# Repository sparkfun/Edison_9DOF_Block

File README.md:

SparkFun Edison 9 Degrees of Freedom
=====================

[*SparkFun Edison 9 Degrees of Freedom (DEV-13033)*](https://www.sparkfun.com/products/13033)

The 9DOF board for the Edison uses the STMicro LSM9DS0 9 Degrees of Freedom IMU for full-range motion sensing. This chip combines a 3-axis accelerometer, a 3-axis gyroscope, and a 3-axis magnetometer. By default, the IMU is connected to the Edison through the I2C bus but can be configured to use the SPI bus.

Repository Contents
-------------------
 
* **/Hardware** - Eagle design files (.brd, .sch)
* **/Production** - Production panel files (.brd)

Documentation
--------------
* **[Hookup Guide](https://learn.sparkfun.com/tutorials/sparkfun-blocks-for-intel-edison---9-degrees-of-freedom-block-)** - Basic hookup guide for the Edison 9DOF.
* **[SparkFun Fritzing repo](https://github.com/sparkfun/Fritzing_Parts)** - Fritzing diagrams for SparkFun products.
* **[SparkFun 3D Model repo](https://github.com/sparkfun/3D_Models)** - 3D models of SparkFun products. 
* **[SparkFun Graphical Datasheets](https://github.com/sparkfun/Graphical_Datasheets)** -Graphical Datasheets for various SparkFun products.

License Information
-------------------

This product is _**open source**_! 

Please review the LICENSE.md file for license information. 

If you have any questions or concerns on licensing, please contact techsupport@sparkfun.com.

Distributed as-is; no warranty is given.

- Your friends at SparkFun.

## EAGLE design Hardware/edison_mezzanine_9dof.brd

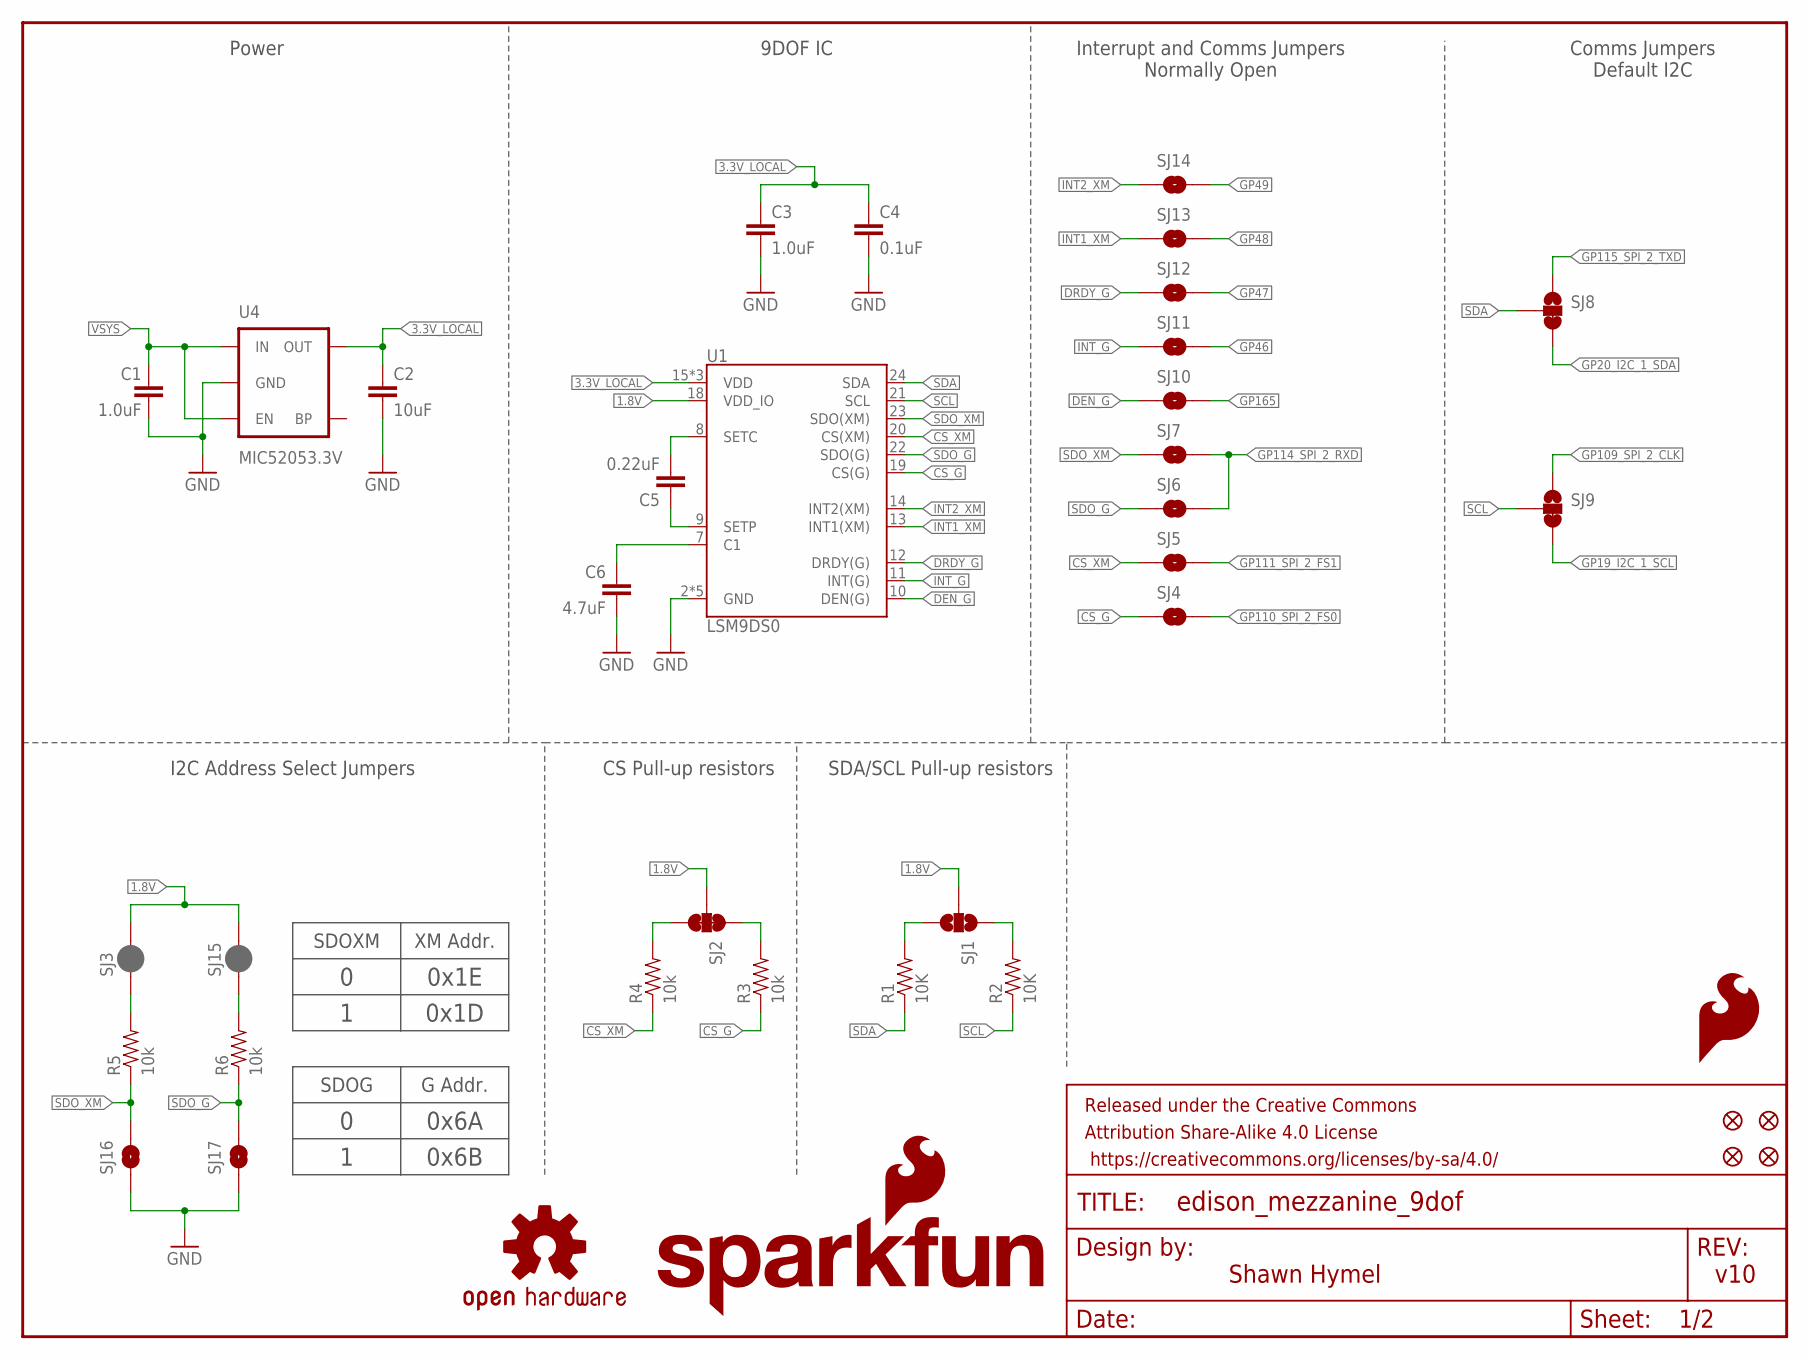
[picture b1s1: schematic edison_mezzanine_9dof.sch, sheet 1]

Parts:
C1, C3: 1.0uF; 0603-CAP
C2: 10uF; 0805
C4: 0.1uF; 0603-CAP
C5: 0.22uF; 0603-CAP
C6: 4.7uF; 0603-CAP
FID1, FID2, FID3, FID4: FIDUCIAL1X2; FIDUCIAL-1X2
FRAME1: FRAME-LETTER; CREATIVE_COMMONS
LOGO1: SFE_LOGO_FLAME.2_INCH; SFE_LOGO_FLAME_.2
LOGO2: OSHW-LOGOS; OSHW-LOGO-S
LOGO3: SFE_LOGO_NAME_FLAME.1_INCH; SFE_LOGO_NAME_FLAME_.1
R1, R2: 10K; 0603-RES
R3, R4, R5, R6: 10k; 0603-RES
SJ1: JUMPER-PAD-3-NOYES_SILK; PAD-JUMPER-3-NO_YES_SILK
SJ2: JUMPER-PAD-3-NC_BY_TRACE; PAD-JUMPER-3-3OF3_NC_BY_TRACE_YES_SILK_FULL_BOX
SJ3, SJ15: JUMPER-PAD-2-NC_BY_PASTE; PAD-JUMPER-2-NC_BY_PASTE_YES_SILK
SJ4, SJ5, SJ6, SJ7, SJ10, SJ11, SJ12, SJ13, SJ14, SJ16, SJ17: JUMPER-PAD-2-NOYES_SILK; PAD-JUMPER-2-NO_YES_SILK
SJ8, SJ9: JUMPER-PAD-3-2OF3_NC_BY_TRACE_SMALL; PAD-JUMPER-3-2OF3_NC_BY_TRACE_YES_SILK_FULL_BOX
U1: LSM9DS0; LGA-24
U4: MIC52053.3V; SOT23-5

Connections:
1.8V: SJ1.2, SJ2.2, SJ3.2, SJ15.2, U1.18 (VDD_IO); also elsewhere on the board
3.3V_LOCAL: C2.1, C3.1, C4.1, U1.15 (VDD), U1.16 (VDD), U1.17 (VDD), U4.5 (OUT)
CS_G: R3.1, SJ4.1, U1.19 (CS(G))
CS_XM: R4.1, SJ5.1, U1.20 (CS(XM))
DEN_G: SJ10.1, U1.10 (DEN(G))
DRDY_G: SJ12.1, U1.12 (DRDY(G))
GND: C1.2, C2.2, C3.2, C4.2, C6.2, SJ16.1, SJ17.1, U1.2 (GND), U1.3 (GND), U1.4 (GND), U1.5 (GND), U1.6 (GND), U4.2 (GND); also elsewhere on the board
GP19_I2C_1_SCL: SJ9.3; also elsewhere on the board
GP20_I2C_1_SDA: SJ8.3; also elsewhere on the board
GP46: SJ11.2; also elsewhere on the board
GP47: SJ12.2; also elsewhere on the board
GP48: SJ13.2; also elsewhere on the board
GP49: SJ14.2; also elsewhere on the board
GP109_SPI_2_CLK: SJ9.1; also elsewhere on the board
GP110_SPI_2_FS0: SJ4.2; also elsewhere on the board
GP111_SPI_2_FS1: SJ5.2; also elsewhere on the board
GP114_SPI_2_RXD: SJ6.2, SJ7.2; also elsewhere on the board
GP115_SPI_2_TXD: SJ8.1; also elsewhere on the board
GP165: SJ10.2; also elsewhere on the board
INT1_XM: SJ13.1, U1.13 (INT1(XM))
INT2_XM: SJ14.1, U1.14 (INT2(XM))
INT_G: SJ11.1, U1.11 (INT(G))
unnamed: C5.1, U1.9 (SETP)
unnamed: C5.2, U1.8 (SETC)
unnamed: C6.1, U1.7 (C1)
unnamed: R3.2, SJ2.1
unnamed: R4.2, SJ2.3
unnamed: R1.2, SJ1.3
unnamed: R2.2, SJ1.1
unnamed: R5.2, SJ3.1
unnamed: R6.2, SJ15.1
SCL: R2.1, SJ9.2, U1.21 (SCL)
SDA: R1.1, SJ8.2, U1.24 (SDA)
SDO_G: R6.1, SJ6.1, SJ17.2, U1.22 (SDO(G))
SDO_XM: R5.1, SJ7.1, SJ16.2, U1.23 (SDO(XM))
VSYS: C1.1, U4.1 (IN), U4.3 (EN); also elsewhere on the board

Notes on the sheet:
I2C Address Select Jumpers
SDA/SCL Pull-up resistors
9DOF IC
Interrupt and Comms Jumpers Normally Open
Comms Jumpers Default I2C
Power
CS Pull-up resistors
SDOXM
XM Addr.
0x1E
0x1D
SDOG
G Addr.
0x6A
0x6B
v10
Shawn Hymel

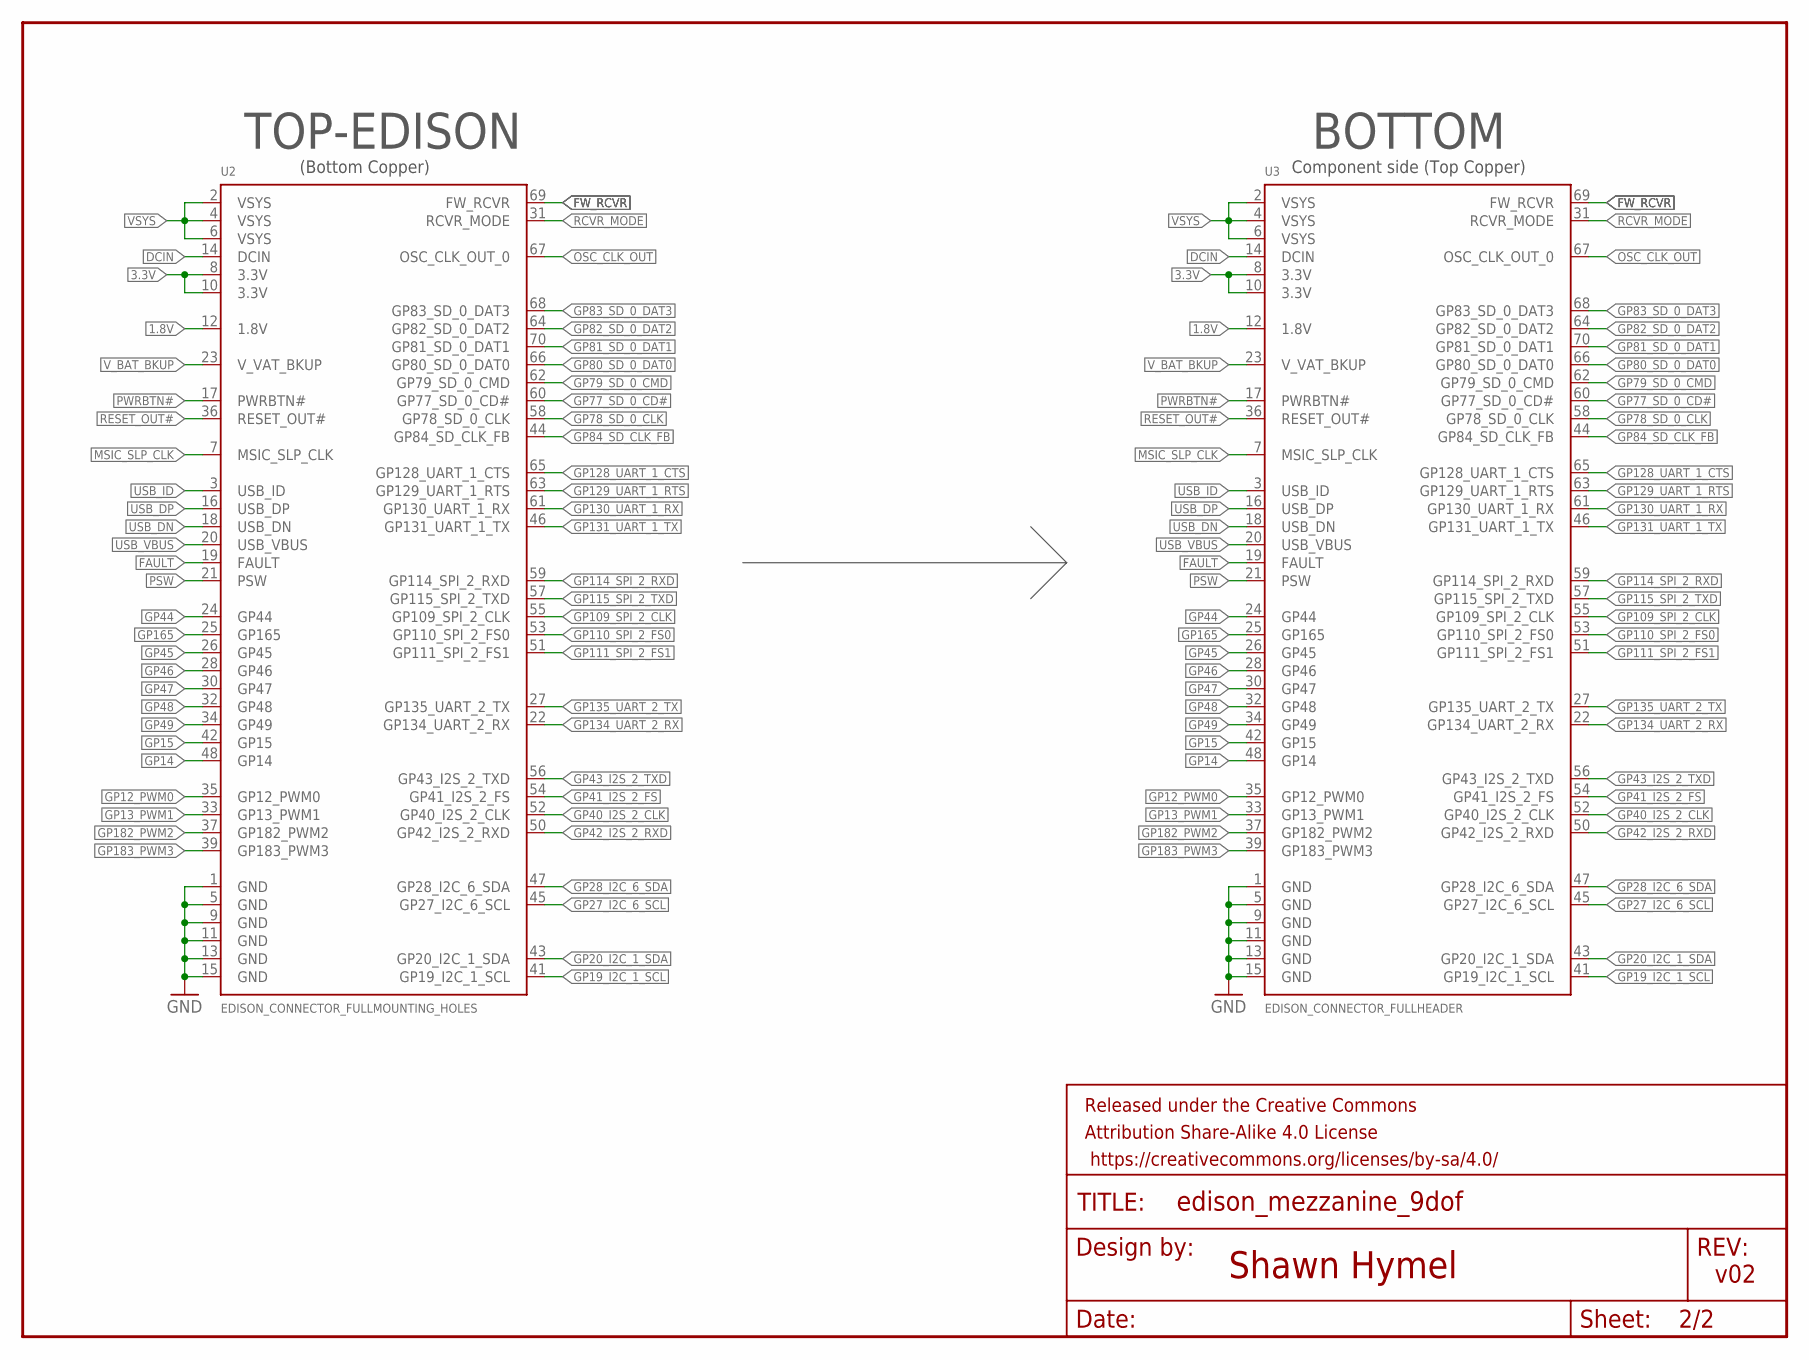
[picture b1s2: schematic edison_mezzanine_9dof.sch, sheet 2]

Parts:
FRAME2: FRAME-LETTER; CREATIVE_COMMONS
U2: EDISON_CONNECTOR_FULLMOUNTING_HOLES; EDISON_DAUGHTER
U3: EDISON_CONNECTOR_FULLHEADER; DF40C-70DP-0.4(51)

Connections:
1.8V: U2.12 (1.8V), U3.12 (1.8V); also elsewhere on the board
3.3V: U2.8 (3.3V), U2.10 (3.3V), U3.8 (3.3V), U3.10 (3.3V)
DCIN: U2.14 (DCIN), U3.14 (DCIN)
FAULT: U2.19 (FAULT), U3.19 (FAULT)
FW_RCVR: U2.69 (FW_RCVR), U3.69 (FW_RCVR)
GND: U2.1 (GND), U2.5 (GND), U2.9 (GND), U2.11 (GND), U2.13 (GND), U2.15 (GND), U3.1 (GND), U3.5 (GND), U3.9 (GND), U3.11 (GND), U3.13 (GND), U3.15 (GND); also elsewhere on the board
GP12_PWM0: U2.35 (GP12_PWM0), U3.35 (GP12_PWM0)
GP13_PWM1: U2.33 (GP13_PWM1), U3.33 (GP13_PWM1)
GP14: U2.48 (GP14), U3.48 (GP14)
GP15: U2.42 (GP15), U3.42 (GP15)
GP19_I2C_1_SCL: U2.41 (GP19_I2C_1_SCL), U3.41 (GP19_I2C_1_SCL); also elsewhere on the board
GP20_I2C_1_SDA: U2.43 (GP20_I2C_1_SDA), U3.43 (GP20_I2C_1_SDA); also elsewhere on the board
GP27_I2C_6_SCL: U2.45 (GP27_I2C_6_SCL), U3.45 (GP27_I2C_6_SCL)
GP28_I2C_6_SDA: U2.47 (GP28_I2C_6_SDA), U3.47 (GP28_I2C_6_SDA)
GP40_I2S_2_CLK: U2.52 (GP40_I2S_2_CLK), U3.52 (GP40_I2S_2_CLK)
GP41_I2S_2_FS: U2.54 (GP41_I2S_2_FS), U3.54 (GP41_I2S_2_FS)
GP42_I2S_2_RXD: U2.50 (GP42_I2S_2_RXD), U3.50 (GP42_I2S_2_RXD)
GP43_I2S_2_TXD: U2.56 (GP43_I2S_2_TXD), U3.56 (GP43_I2S_2_TXD)
GP44: U2.24 (GP44), U3.24 (GP44)
GP45: U2.26 (GP45), U3.26 (GP45)
GP46: U2.28 (GP46), U3.28 (GP46); also elsewhere on the board
GP47: U2.30 (GP47), U3.30 (GP47); also elsewhere on the board
GP48: U2.32 (GP48), U3.32 (GP48); also elsewhere on the board
GP49: U2.34 (GP49), U3.34 (GP49); also elsewhere on the board
GP77_SD_0_CD#: U2.60 (GP77_SD_0_CD#), U3.60 (GP77_SD_0_CD#)
GP78_SD_0_CLK: U2.58 (GP78_SD_0_CLK), U3.58 (GP78_SD_0_CLK)
GP79_SD_0_CMD: U2.62 (GP79_SD_0_CMD), U3.62 (GP79_SD_0_CMD)
GP80_SD_0_DAT0: U2.66 (GP80_SD_0_DAT0), U3.66 (GP80_SD_0_DAT0)
GP81_SD_0_DAT1: U2.70 (GP81_SD_0_DAT1), U3.70 (GP81_SD_0_DAT1)
GP82_SD_0_DAT2: U2.64 (GP82_SD_0_DAT2), U3.64 (GP82_SD_0_DAT2)
GP83_SD_0_DAT3: U2.68 (GP83_SD_0_DAT3), U3.68 (GP83_SD_0_DAT3)
GP84_SD_CLK_FB: U2.44 (GP84_SD_CLK_FB), U3.44 (GP84_SD_CLK_FB)
GP109_SPI_2_CLK: U2.55 (GP109_SPI_2_CLK), U3.55 (GP109_SPI_2_CLK); also elsewhere on the board
GP110_SPI_2_FS0: U2.53 (GP110_SPI_2_FS0), U3.53 (GP110_SPI_2_FS0); also elsewhere on the board
GP111_SPI_2_FS1: U2.51 (GP111_SPI_2_FS1), U3.51 (GP111_SPI_2_FS1); also elsewhere on the board
GP114_SPI_2_RXD: U2.59 (GP114_SPI_2_RXD), U3.59 (GP114_SPI_2_RXD); also elsewhere on the board
GP115_SPI_2_TXD: U2.57 (GP115_SPI_2_TXD), U3.57 (GP115_SPI_2_TXD); also elsewhere on the board
GP128_UART_1_CTS: U2.65 (GP128_UART_1_CTS), U3.65 (GP128_UART_1_CTS)
GP129_UART_1_RTS: U2.63 (GP129_UART_1_RTS), U3.63 (GP129_UART_1_RTS)
GP130_UART_1_RX: U2.61 (GP130_UART_1_RX), U3.61 (GP130_UART_1_RX)
GP131_UART_1_TX: U2.46 (GP131_UART_1_TX), U3.46 (GP131_UART_1_TX)
GP134_UART_2_RX: U2.22 (GP134_UART_2_RX), U3.22 (GP134_UART_2_RX)
GP135_UART_2_TX: U2.27 (GP135_UART_2_TX), U3.27 (GP135_UART_2_TX)
GP165: U2.25 (GP165), U3.25 (GP165); also elsewhere on the board
GP182_PWM2: U2.37 (GP182_PWM2), U3.37 (GP182_PWM2)
GP183_PWM3: U2.39 (GP183_PWM3), U3.39 (GP183_PWM3)
MSIC_SLP_CLK: U2.7 (MSIC_SLP_CLK), U3.7 (MSIC_SLP_CLK)
OSC_CLK_OUT: U2.67 (OSC_CLK_OUT_0), U3.67 (OSC_CLK_OUT_0)
PSW: U2.21 (PSW), U3.21 (PSW)
PWRBTN#: U2.17 (PWRBTN#), U3.17 (PWRBTN#)
RCVR_MODE: U2.31 (RCVR_MODE), U3.31 (RCVR_MODE)
RESET_OUT#: U2.36 (RESET_OUT#), U3.36 (RESET_OUT#)
USB_DN: U2.18 (USB_DN), U3.18 (USB_DN)
USB_DP: U2.16 (USB_DP), U3.16 (USB_DP)
USB_ID: U2.3 (USB_ID), U3.3 (USB_ID)
USB_VBUS: U2.20 (USB_VBUS), U3.20 (USB_VBUS)
VSYS: U2.2 (VSYS), U2.4 (VSYS), U2.6 (VSYS), U3.2 (VSYS), U3.4 (VSYS), U3.6 (VSYS); also elsewhere on the board
V_BAT_BKUP: U2.23 (V_VAT_BKUP), U3.23 (V_VAT_BKUP)

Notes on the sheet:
TOP-EDISON
BOTTOM
Component side (Top Copper)
(Bottom Copper)
Shawn Hymel
v02

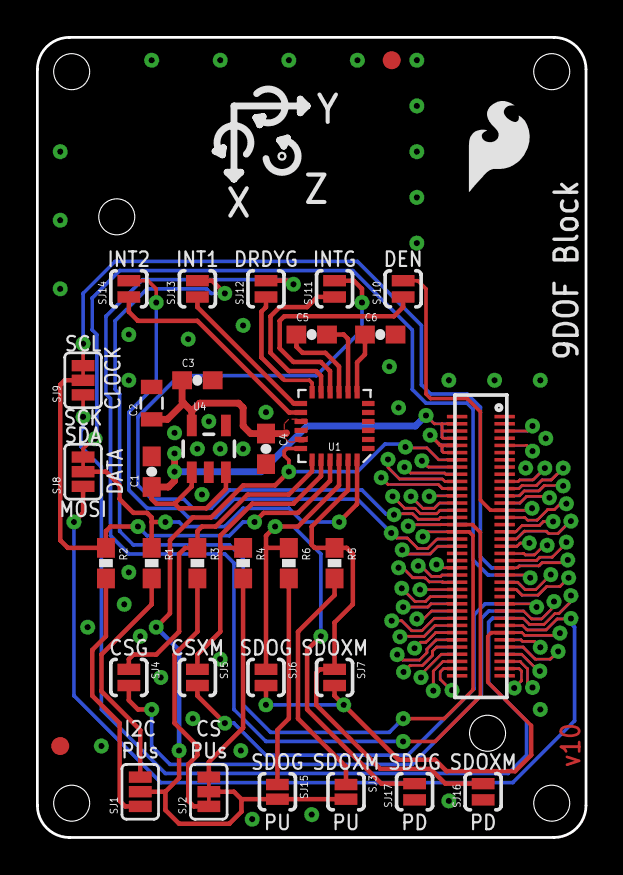
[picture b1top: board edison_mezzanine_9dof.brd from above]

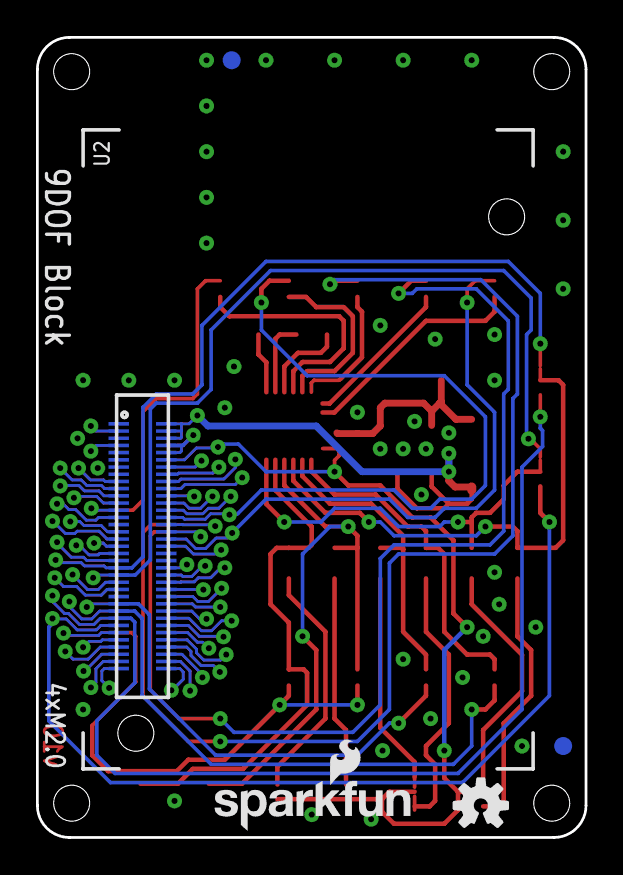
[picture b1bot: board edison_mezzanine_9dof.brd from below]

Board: 2 copper layers, 30.5 x 44.5 mm, 42 parts (6 on the bottom side), 79 nets.

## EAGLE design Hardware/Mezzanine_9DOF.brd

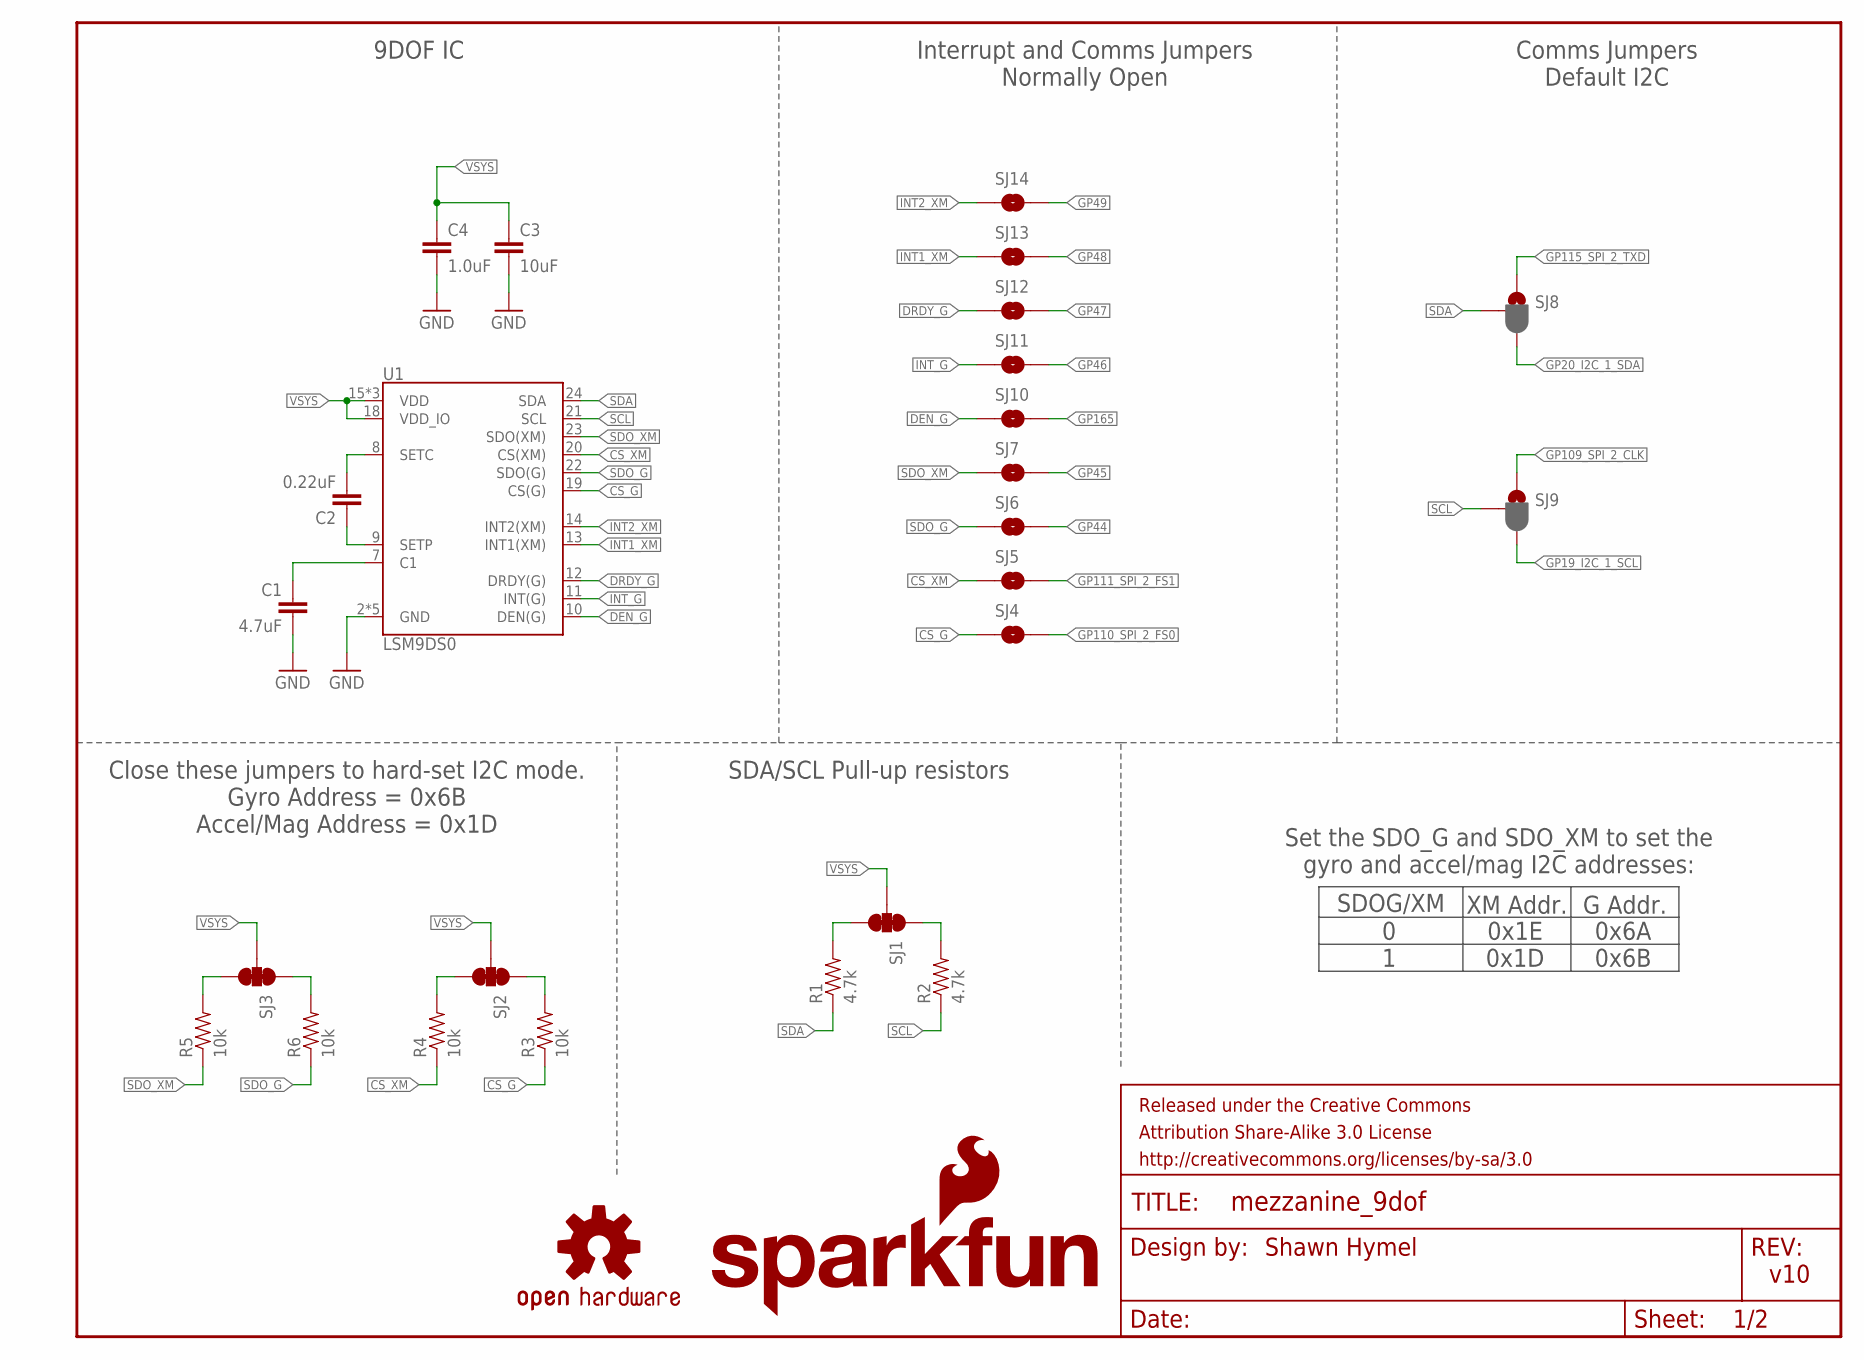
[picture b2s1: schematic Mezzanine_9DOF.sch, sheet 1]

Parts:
C1: 4.7uF; 0603-CAP
C2: 0.22uF; 0603-CAP
C3: 10uF; 0805
C4: 1.0uF; 0603-CAP
FRAME1: FRAME-LETTER; CREATIVE_COMMONS
LOGO2: OSHW-LOGOS; OSHW-LOGO-S
LOGO3: SFE_LOGO_NAME_FLAME.1_INCH; SFE_LOGO_NAME_FLAME_.1
R1, R2: 4.7k; 0603-RES
R3, R4, R5, R6: 10k; 0603-RES
SJ1, SJ2, SJ3: SOLDERJUMPER_2WAYS; SJ_3
SJ4, SJ5, SJ6, SJ7, SJ10, SJ11, SJ12, SJ13, SJ14: JUMPER-PAD-2-NOYES_SILK; PAD-JUMPER-2-NO_YES_SILK
SJ8, SJ9: JUMPER-PAD-3-2OF3_NC_BY_PASTE; PAD-JUMPER-3-2OF3_NC_BY_PASTE_YES_SILK_FULL_BOX
U1: LSM9DS0; LGA-24

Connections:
CS_G: R3.1, SJ4.1, U1.19 (CS(G))
CS_XM: R4.1, SJ5.1, U1.20 (CS(XM))
DEN_G: SJ10.1, U1.10 (DEN(G))
DRDY_G: SJ12.1, U1.12 (DRDY(G))
GND: C1.2, C3.2, C4.2, U1.2 (GND), U1.3 (GND), U1.4 (GND), U1.5 (GND), U1.6 (GND); also elsewhere on the board
GP19_I2C_1_SCL: SJ9.3; also elsewhere on the board
GP20_I2C_1_SDA: SJ8.3; also elsewhere on the board
GP44: SJ6.2; also elsewhere on the board
GP45: SJ7.2; also elsewhere on the board
GP46: SJ11.2; also elsewhere on the board
GP47: SJ12.2; also elsewhere on the board
GP48: SJ13.2; also elsewhere on the board
GP49: SJ14.2; also elsewhere on the board
GP109_SPI_2_CLK: SJ9.1; also elsewhere on the board
GP110_SPI_2_FS0: SJ4.2; also elsewhere on the board
GP111_SPI_2_FS1: SJ5.2; also elsewhere on the board
GP115_SPI_2_TXD: SJ8.1; also elsewhere on the board
GP165: SJ10.2; also elsewhere on the board
INT1_XM: SJ13.1, U1.13 (INT1(XM))
INT2_XM: SJ14.1, U1.14 (INT2(XM))
INT_G: SJ11.1, U1.11 (INT(G))
unnamed: C2.1, U1.9 (SETP)
unnamed: C2.2, U1.8 (SETC)
unnamed: C1.1, U1.7 (C1)
unnamed: R3.2, SJ2.1
unnamed: R4.2, SJ2.3
unnamed: R1.2, SJ1.3
unnamed: R2.2, SJ1.1
unnamed: R5.2, SJ3.3
unnamed: R6.2, SJ3.1
SCL: R2.1, SJ9.2, U1.21 (SCL)
SDA: R1.1, SJ8.2, U1.24 (SDA)
SDO_G: R6.1, SJ6.1, U1.22 (SDO(G))
SDO_XM: R5.1, SJ7.1, U1.23 (SDO(XM))
VSYS: C3.1, C4.1, SJ1.2, SJ2.2, SJ3.2, U1.15 (VDD), U1.16 (VDD), U1.17 (VDD), U1.18 (VDD_IO); also elsewhere on the board

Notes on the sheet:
Close these jumpers to hard-set I2C mode. Gyro Address = 0x6B Accel/Mag Address = 0x1D
SDA/SCL Pull-up resistors
SDOG/XM
0x1E 0x1D
XM Addr.
0 1
G Addr.
0x6A 0x6B
Set the SDO_G and SDO_XM to set the gyro and accel/mag I2C addresses:
Shawn Hymel
v10
9DOF IC
Interrupt and Comms Jumpers Normally Open
Comms Jumpers Default I2C

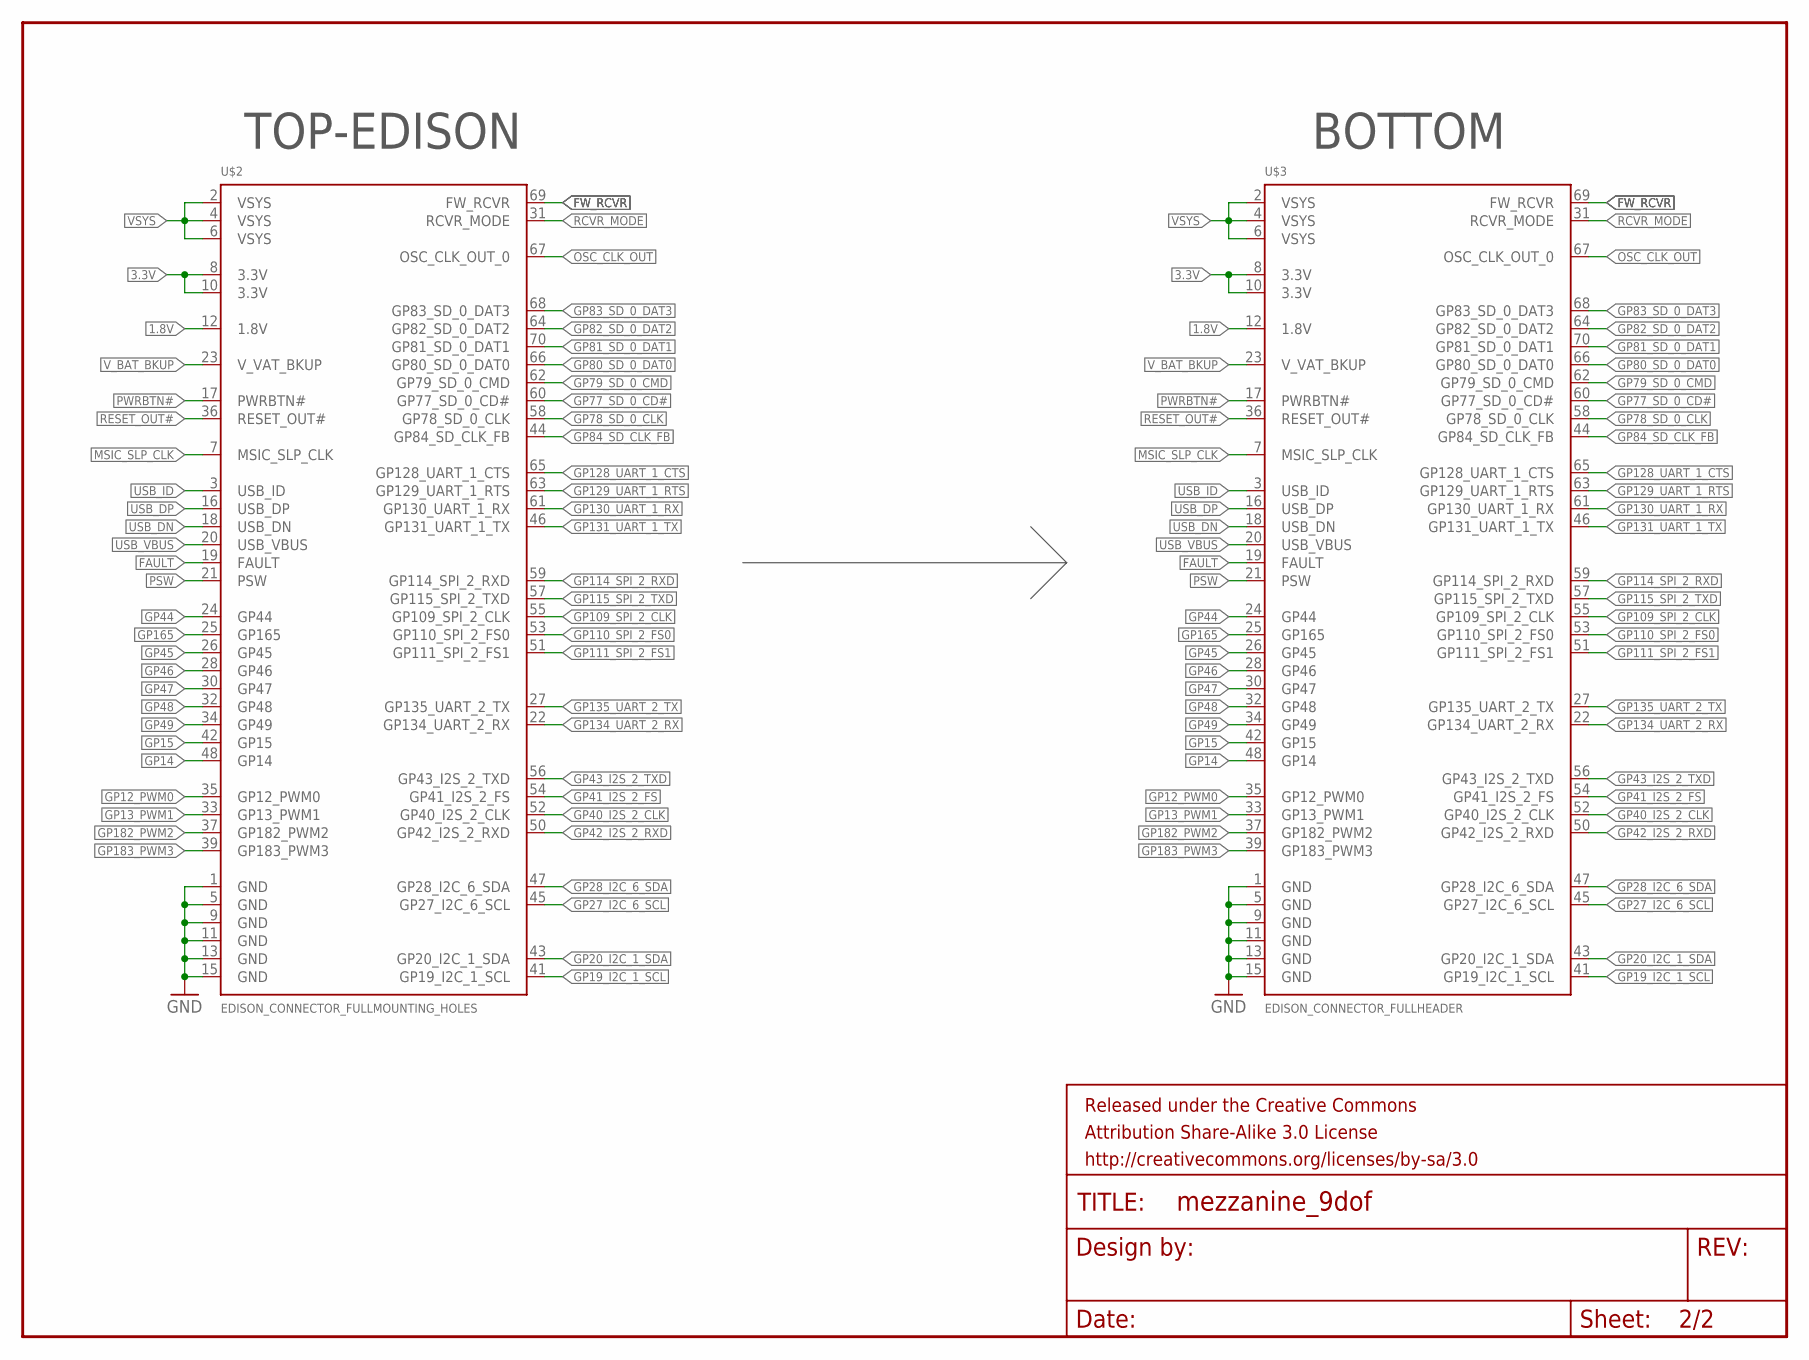
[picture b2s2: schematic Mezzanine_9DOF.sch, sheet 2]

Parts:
FRAME2: FRAME-LETTER; CREATIVE_COMMONS
U$2: EDISON_CONNECTOR_FULLMOUNTING_HOLES; EDISON_DAUGHTER
U$3: EDISON_CONNECTOR_FULLHEADER; DF40C-70DP-0.4(51)

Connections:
1.8V: U$2.12 (1.8V), U$3.12 (1.8V)
3.3V: U$2.8 (3.3V), U$2.10 (3.3V), U$3.8 (3.3V), U$3.10 (3.3V)
FAULT: U$2.19 (FAULT), U$3.19 (FAULT)
FW_RCVR: U$2.69 (FW_RCVR), U$3.69 (FW_RCVR)
GND: U$2.1 (GND), U$2.5 (GND), U$2.9 (GND), U$2.11 (GND), U$2.13 (GND), U$2.15 (GND), U$3.1 (GND), U$3.5 (GND), U$3.9 (GND), U$3.11 (GND), U$3.13 (GND), U$3.15 (GND); also elsewhere on the board
GP12_PWM0: U$2.35 (GP12_PWM0), U$3.35 (GP12_PWM0)
GP13_PWM1: U$2.33 (GP13_PWM1), U$3.33 (GP13_PWM1)
GP14: U$2.48 (GP14), U$3.48 (GP14)
GP15: U$2.42 (GP15), U$3.42 (GP15)
GP19_I2C_1_SCL: U$2.41 (GP19_I2C_1_SCL), U$3.41 (GP19_I2C_1_SCL); also elsewhere on the board
GP20_I2C_1_SDA: U$2.43 (GP20_I2C_1_SDA), U$3.43 (GP20_I2C_1_SDA); also elsewhere on the board
GP27_I2C_6_SCL: U$2.45 (GP27_I2C_6_SCL), U$3.45 (GP27_I2C_6_SCL)
GP28_I2C_6_SDA: U$2.47 (GP28_I2C_6_SDA), U$3.47 (GP28_I2C_6_SDA)
GP40_I2S_2_CLK: U$2.52 (GP40_I2S_2_CLK), U$3.52 (GP40_I2S_2_CLK)
GP41_I2S_2_FS: U$2.54 (GP41_I2S_2_FS), U$3.54 (GP41_I2S_2_FS)
GP42_I2S_2_RXD: U$2.50 (GP42_I2S_2_RXD), U$3.50 (GP42_I2S_2_RXD)
GP43_I2S_2_TXD: U$2.56 (GP43_I2S_2_TXD), U$3.56 (GP43_I2S_2_TXD)
GP44: U$2.24 (GP44), U$3.24 (GP44); also elsewhere on the board
GP45: U$2.26 (GP45), U$3.26 (GP45); also elsewhere on the board
GP46: U$2.28 (GP46), U$3.28 (GP46); also elsewhere on the board
GP47: U$2.30 (GP47), U$3.30 (GP47); also elsewhere on the board
GP48: U$2.32 (GP48), U$3.32 (GP48); also elsewhere on the board
GP49: U$2.34 (GP49), U$3.34 (GP49); also elsewhere on the board
GP77_SD_0_CD#: U$2.60 (GP77_SD_0_CD#), U$3.60 (GP77_SD_0_CD#)
GP78_SD_0_CLK: U$2.58 (GP78_SD_0_CLK), U$3.58 (GP78_SD_0_CLK)
GP79_SD_0_CMD: U$2.62 (GP79_SD_0_CMD), U$3.62 (GP79_SD_0_CMD)
GP80_SD_0_DAT0: U$2.66 (GP80_SD_0_DAT0), U$3.66 (GP80_SD_0_DAT0)
GP81_SD_0_DAT1: U$2.70 (GP81_SD_0_DAT1), U$3.70 (GP81_SD_0_DAT1)
GP82_SD_0_DAT2: U$2.64 (GP82_SD_0_DAT2), U$3.64 (GP82_SD_0_DAT2)
GP83_SD_0_DAT3: U$2.68 (GP83_SD_0_DAT3), U$3.68 (GP83_SD_0_DAT3)
GP84_SD_CLK_FB: U$2.44 (GP84_SD_CLK_FB), U$3.44 (GP84_SD_CLK_FB)
GP109_SPI_2_CLK: U$2.55 (GP109_SPI_2_CLK), U$3.55 (GP109_SPI_2_CLK); also elsewhere on the board
GP110_SPI_2_FS0: U$2.53 (GP110_SPI_2_FS0), U$3.53 (GP110_SPI_2_FS0); also elsewhere on the board
GP111_SPI_2_FS1: U$2.51 (GP111_SPI_2_FS1), U$3.51 (GP111_SPI_2_FS1); also elsewhere on the board
GP114_SPI_2_RXD: U$2.59 (GP114_SPI_2_RXD), U$3.59 (GP114_SPI_2_RXD)
GP115_SPI_2_TXD: U$2.57 (GP115_SPI_2_TXD), U$3.57 (GP115_SPI_2_TXD); also elsewhere on the board
GP128_UART_1_CTS: U$2.65 (GP128_UART_1_CTS), U$3.65 (GP128_UART_1_CTS)
GP129_UART_1_RTS: U$2.63 (GP129_UART_1_RTS), U$3.63 (GP129_UART_1_RTS)
GP130_UART_1_RX: U$2.61 (GP130_UART_1_RX), U$3.61 (GP130_UART_1_RX)
GP131_UART_1_TX: U$2.46 (GP131_UART_1_TX), U$3.46 (GP131_UART_1_TX)
GP134_UART_2_RX: U$2.22 (GP134_UART_2_RX), U$3.22 (GP134_UART_2_RX)
GP135_UART_2_TX: U$2.27 (GP135_UART_2_TX), U$3.27 (GP135_UART_2_TX)
GP165: U$2.25 (GP165), U$3.25 (GP165); also elsewhere on the board
GP182_PWM2: U$2.37 (GP182_PWM2), U$3.37 (GP182_PWM2)
GP183_PWM3: U$2.39 (GP183_PWM3), U$3.39 (GP183_PWM3)
MSIC_SLP_CLK: U$2.7 (MSIC_SLP_CLK), U$3.7 (MSIC_SLP_CLK)
OSC_CLK_OUT: U$2.67 (OSC_CLK_OUT_0), U$3.67 (OSC_CLK_OUT_0)
PSW: U$2.21 (PSW), U$3.21 (PSW)
PWRBTN#: U$2.17 (PWRBTN#), U$3.17 (PWRBTN#)
RCVR_MODE: U$2.31 (RCVR_MODE), U$3.31 (RCVR_MODE)
RESET_OUT#: U$2.36 (RESET_OUT#), U$3.36 (RESET_OUT#)
USB_DN: U$2.18 (USB_DN), U$3.18 (USB_DN)
USB_DP: U$2.16 (USB_DP), U$3.16 (USB_DP)
USB_ID: U$2.3 (USB_ID), U$3.3 (USB_ID)
USB_VBUS: U$2.20 (USB_VBUS), U$3.20 (USB_VBUS)
VSYS: U$2.2 (VSYS), U$2.4 (VSYS), U$2.6 (VSYS), U$3.2 (VSYS), U$3.4 (VSYS), U$3.6 (VSYS); also elsewhere on the board
V_BAT_BKUP: U$2.23 (V_VAT_BKUP), U$3.23 (V_VAT_BKUP)

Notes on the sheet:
TOP-EDISON
BOTTOM

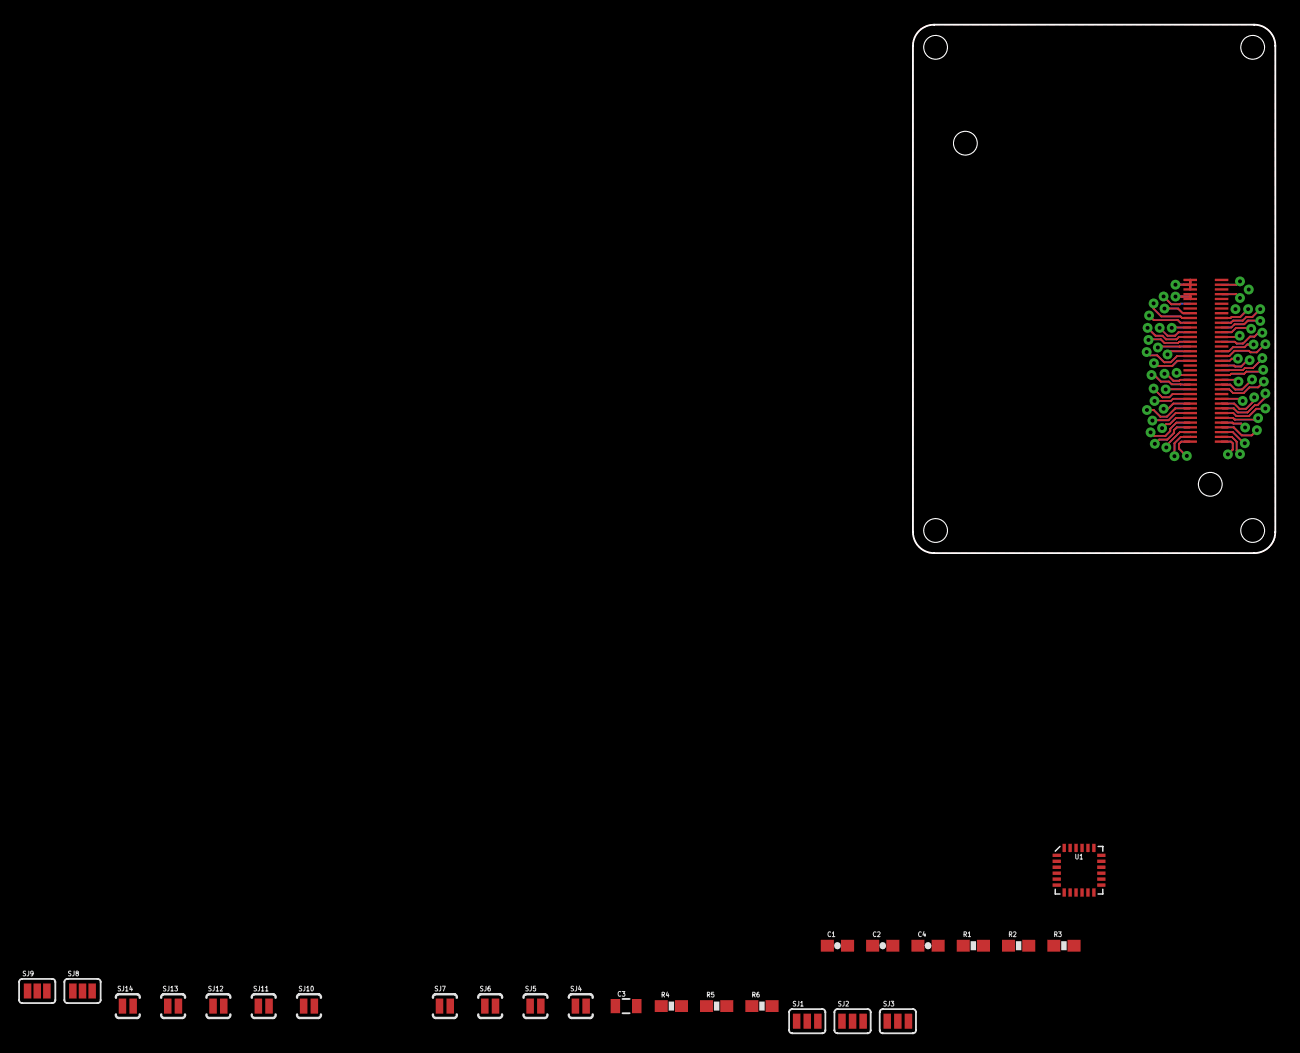
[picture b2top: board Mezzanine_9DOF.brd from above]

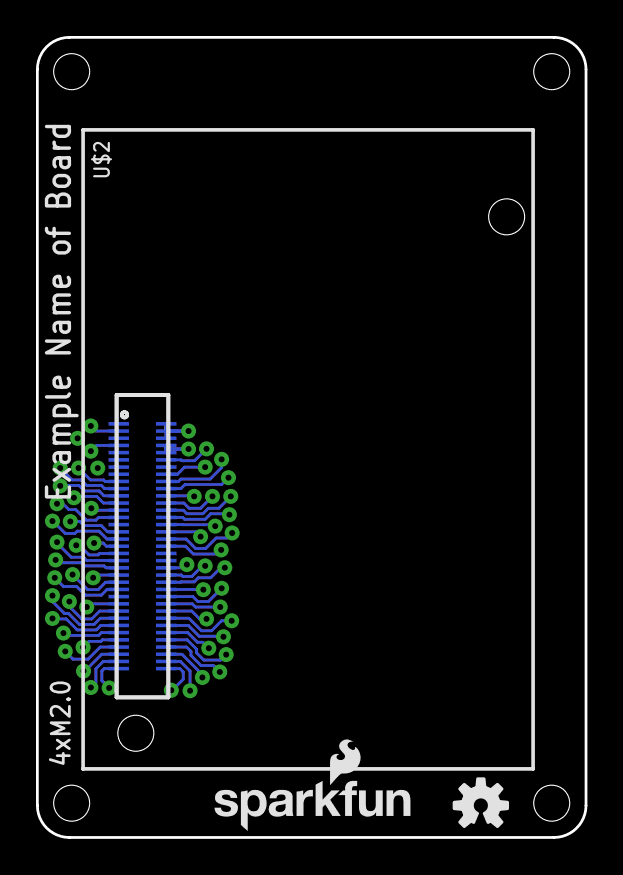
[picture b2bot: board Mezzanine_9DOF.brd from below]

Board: 2 copper layers, 30.5 x 44.5 mm, 31 parts (4 on the bottom side), 77 nets.

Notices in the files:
parts and their libraries:
SparkFun-Aesthetics: Licensing: Creative Commons ShareAlike 4.0 International - https://creativecommons.org/licenses/by-sa/4.0
SparkFun-Aesthetics: Released under the Creative Commons Attribution Share-Alike 3.0 License
SparkFun-Aesthetics: http://creativecommons.org/licenses/by-sa/3.0
